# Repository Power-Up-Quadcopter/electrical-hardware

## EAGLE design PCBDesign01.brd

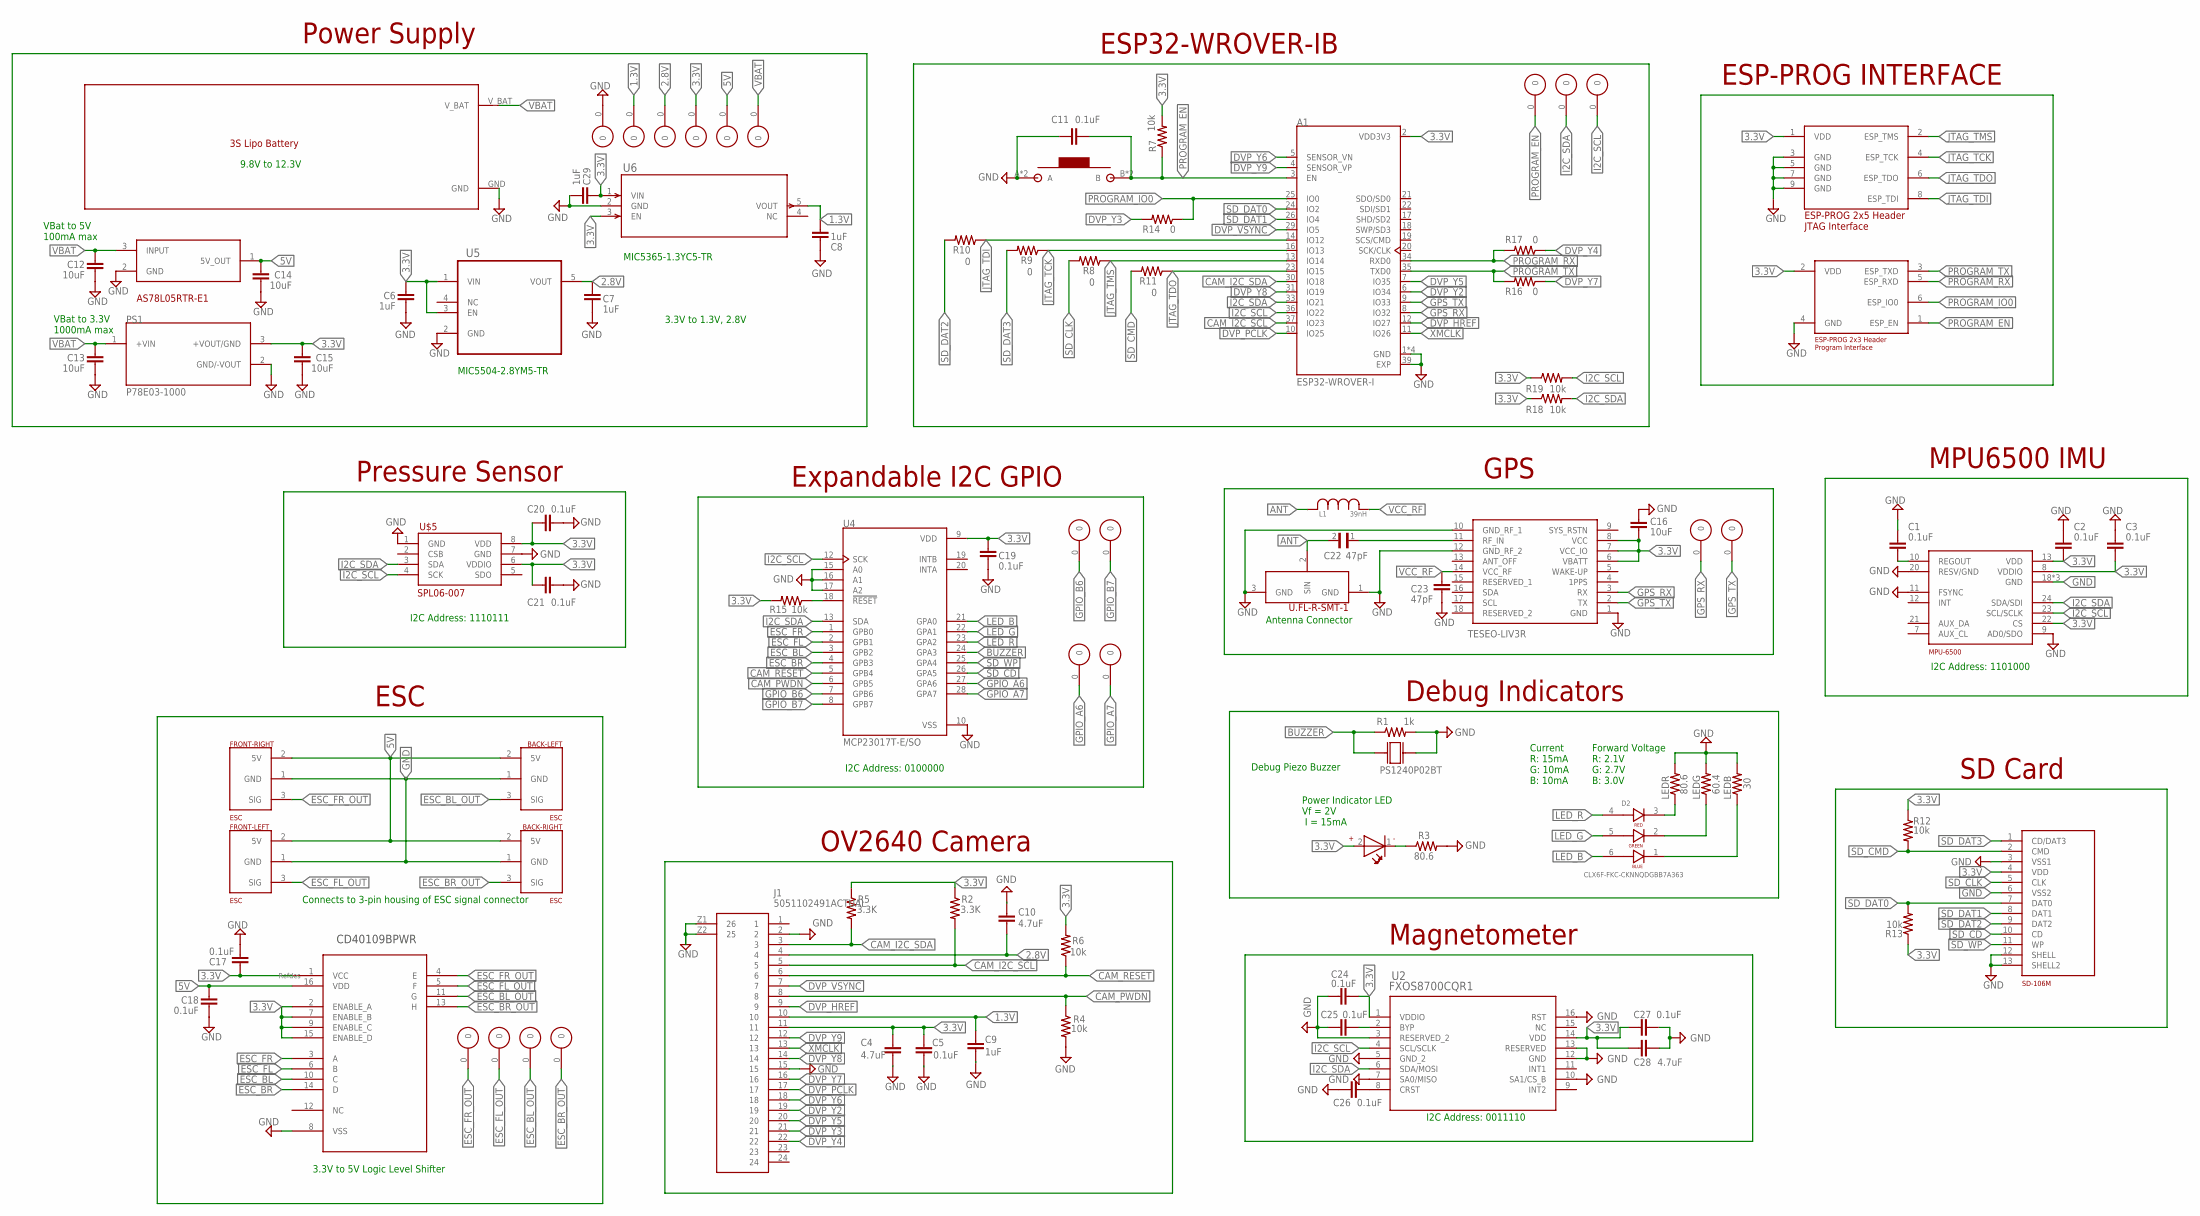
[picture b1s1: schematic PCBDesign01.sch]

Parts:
A1: ESP32-WROVER-I; XCVR_ESP32-WROVER-I
BACK-LEFT: ESC; MA03-1
BACK-RIGHT: ESC; MA03-1
BUZZER: PS1240P02BT; XDCR_PS1240P02BT
C1, C2, C3, C5, C11, C17, C18, C19, C20, C21, C24, C25, C26, C27: 0.1uF; CAPC2012X110
C4, C10, C28: 4.7uF; CAPC2012X110
C6, C7, C8, C9, C29: 1uF; CAPC2012X110
C12, C13, C14, C15, C16: 10uF; CAPC2012X110
C22: 47pF; CAPC1005X55N
C23: 47pF; CAPC2012X110
D2: CLX6F-FKC-CKNNQDGBB7A363; SOJ100P350X290-6N
FRONT-LEFT: ESC; MA03-1
FRONT-RIGHT: ESC; MA03-1
IC1: TESEO-LIV3R; TESEOLIV3R
J1: 5051102491ACTUAL; 687124149022
L1: 39nH; IND0402_22N_TAI_TAY-M
LEDB: 30; RESC2012X65
LEDG: 60.4; RESC2012X65
LEDR: 80.6; RESC2012X65
PS1: P78E03-1000; CONV_P78E03-1000
PWR-INDICATOR: WL-SMCW-150060GS75000-G; WL-SMCW_0603
R1: 1k; RESC2012X65
R2, R5: 3.3K; RESC2012X65
R3: 80.6; RESC2012X65
R4, R6, R7, R12, R13, R15, R18, R19: 10k; RESC2012X65
R8, R9, R10, R11, R14, R16, R17: 0; RESC2012X65
U2: FXOS8700CQR1; QFN16_3X3_NXP
U3: CD40109BPWR; SOP65P640X120-16N
U4: MCP23017T-E/SO; SOIC127P1030X265-28N
U5: MIC5504-2.8YM5-TR; SOT95P280X145-5N
U6: MIC5365-1.3YC5-TRSC-70_C5_MCH-M; SC-70_C5_MCH-M
U$1: MPU6500; QFN40P300X300X105-24N
U$2, U$9, U$10, U$11, U$12, U$13, U$14, U$15, U$16, U$17, U$18, U$19, U$20, U$21, U$23, U$24, U$25, U$26, U$27: TESTPOINT
U$3: SD-106M; SDCARD
U$4: U.FL-R-SMT-1; U.FL
U$5: SPL06-007
U$6: ESP-PROG_JTAG_HEADER; SAMTEC-FTS-105-01-X-D
U$7: ESP-PROG_PROGRAM_HEADER; SAMTEC-FTS-103-01-X-D
U$8: RESET; BUTTON
U$28: AS78L05RTR-E1; VREG_AP2204RA-3.3TRG1
U$29: LARGE_BATTERY

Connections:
1.3V: C8.1, C9.2, J1.10, U6.5 (VOUT), U$17.0
2.8V: C7.1, C10.1, J1.4, U5.5 (VOUT), U$18.0
3.3V: A1.2 (VDD3V3), C2.2, C3.2, C4.1, C5.1, C6.1, C15.2, C16.2, C17.2, C19.2, C20.2, C21.2, C24.2, C27.1, C28.1, C29.1, IC1.6 (VBATT), IC1.7 (VCC_IO), IC1.8 (VCC), J1.11, PS1.3 (+VOUT/GND), PWR-INDICATOR.2 (+), R2.1, R5.1, R6.2, R7.2, R12.1, R13.1, R15.2, R18.1, R19.1, U2.1 (VDDIO), U2.14 (VDD), U3.1 (VCC), U3.2 (ENABLE_A), U3.7 (ENABLE_B), U3.9 (ENABLE_C), U3.15 (ENABLE_D), U4.9 (VDD), U5.1 (VIN), U5.3 (EN), U6.1 (VIN), U6.3 (EN), U$1.8 (VDDIO), U$1.13 (VDD), U$1.22 (CS), U$3.4 (VDD), U$5.6 (VDDIO), U$5.8 (VDD), U$6.1 (VDD), U$7.2 (VDD), U$15.0
5V: BACK-LEFT.2 (5V), BACK-RIGHT.2 (5V), C14.2, C18.2, FRONT-LEFT.2 (5V), FRONT-RIGHT.2 (5V), U3.16 (VDD), U$16.0, U$28.1 (5V_OUT)
ANT: C22.2, L1.2, U$4.2 (SIN)
BUZZER: BUZZER.1, R1.1, U4.24 (GPA3)
CAM_I2C_SCL: A1.37 (IO23), J1.5, R2.2
CAM_I2C_SDA: A1.30 (IO18), J1.3, R5.2
CAM_PWDN: J1.8, R4.1, U4.6 (GPB5)
CAM_RESET: J1.6, R6.1, U4.5 (GPB4)
DVP_HREF: A1.12 (IO27), J1.9
DVP_PCLK: A1.10 (IO25), J1.17
DVP_VSYNC: A1.29 (IO5), J1.7
DVP_Y2: A1.6 (IO34), J1.19
DVP_Y3: J1.21, R14.2
DVP_Y4: J1.22, R17.1
DVP_Y5: A1.7 (IO35), J1.20
DVP_Y6: A1.5 (SENSOR_VN), J1.18
DVP_Y7: J1.16, R16.1
DVP_Y8: A1.31 (IO19), J1.14
DVP_Y9: A1.4 (SENSOR_VP), J1.12
ESC_BL: U3.10 (C), U4.3 (GPB2)
ESC_BL_OUT: BACK-LEFT.3 (SIG), U3.11 (G), U$25.0
ESC_BR: U3.14 (D), U4.4 (GPB3)
ESC_BR_OUT: BACK-RIGHT.3 (SIG), U3.13 (H), U$27.0
ESC_FL: U3.6 (B), U4.2 (GPB1)
ESC_FL_OUT: FRONT-LEFT.3 (SIG), U3.5 (F), U$26.0
ESC_FR: U3.3 (A), U4.1 (GPB0)
ESC_FR_OUT: FRONT-RIGHT.3 (SIG), U3.4 (E), U$24.0
GND: A1.1 (GND), A1.15 (GND), A1.38 (GND), A1.39 (EXP), A1.P$1 (GND), BACK-LEFT.1 (GND), BACK-RIGHT.1 (GND), BUZZER.2, C1.1, C2.1, C3.1, C4.2, C5.2, C6.2, C7.2, C8.2, C9.1, C10.2, C11.1, C12.1, C13.1, C14.1, C15.1, C16.1, C17.1, C18.1, C19.1, C20.1, C21.1, C23.1, C24.1, C25.2, C26.2, C27.2, C28.2, C29.2, FRONT-LEFT.1 (GND), FRONT-RIGHT.1 (GND), IC1.1 (GND), IC1.10 (GND_RF_1), IC1.12 (GND_RF_2), J1.2, J1.15, J1.Z1 (26), J1.Z2 (25), LEDB.2, LEDG.2, LEDR.2, PS1.2 (GND/-VOUT), R1.2, R3.2, R4.2, U2.3 (RESERVED_2), U2.5 (GND_2), U2.7 (SA0/MISO), U2.10 (SA1/CS_B), U2.12 (GND), U2.13 (RESERVED), U2.16 (RST), U3.8 (VSS), U4.10 (VSS), U4.15 (A0), U4.16 (A1), U4.17 (A2), U5.2 (GND), U6.2 (GND), U$1.9 (AD0/SDO), U$1.11 (FSYNC), U$1.18 (GND), U$1.20 (RESV/GND), U$1.25 (GND), U$1.P$1 (GND), U$3.3 (VSS1), U$3.6 (VSS2), U$3.12 (SHELL), U$3.13 (SHELL2), U$4.1 (GND), U$4.3 (GND), U$5.1 (GND), U$5.7 (GND), U$6.3 (GND), U$6.5 (GND), U$6.7 (GND), U$6.9 (GND), U$7.4 (GND), U$8.A, U$8.A@1 (A), U$21.0, U$28.2 (GND), U$29.GND
GPIO_A6: U4.27 (GPA6), U$2.0
GPIO_A7: U4.28 (GPA7), U$19.0
GPIO_B6: U4.7 (GPB6), U$14.0
GPIO_B7: U4.8 (GPB7), U$20.0
GPS_RX: A1.8 (IO32), IC1.3 (RX), U$11.0
GPS_TX: A1.9 (IO33), IC1.2 (TX), U$12.0
I2C_SCL: A1.36 (IO22), R19.2, U2.4 (SCL/SCLK), U4.12 (SCK), U$1.23 (SCL/SCLK), U$5.4 (SCK), U$10.0
I2C_SDA: A1.33 (IO21), R18.2, U2.6 (SDA/MOSI), U4.13 (SDA), U$1.24 (SDA/SDI), U$5.3 (SDA), U$9.0
JTAG_TCK: A1.16 (IO13), R9.1, U$6.4 (ESP_TCK)
JTAG_TDI: A1.14 (IO12), R10.1, U$6.8 (ESP_TDI)
JTAG_TDO: A1.23 (IO15), R11.1, U$6.6 (ESP_TDO)
JTAG_TMS: A1.13 (IO14), R8.1, U$6.2 (ESP_TMS)
LED_B: D2.6, U4.21 (GPA0)
LED_G: D2.5, U4.22 (GPA1)
LED_R: D2.4, U4.23 (GPA2)
unnamed: D2.3, LEDR.1
unnamed: D2.2, LEDG.1
unnamed: C1.2, U$1.10 (REGOUT)
unnamed: D2.1, LEDB.1
unnamed: C26.1, U2.8 (CRST)
unnamed: PWR-INDICATOR.1 (-), R3.1
unnamed: C25.1, U2.2 (BYP)
unnamed: C22.1, IC1.11 (RF_IN)
unnamed: R15.1, U4.18 (!RESET)
PROGRAM_EN: A1.3 (EN), C11.2, R7.1, U$7.1 (ESP_EN), U$8.B, U$8.B@1 (B), U$23.0
PROGRAM_IO0: A1.25 (IO0), R14.1, U$7.6 (ESP_IO0)
PROGRAM_RX: A1.34 (RXD0), R17.2, U$7.5 (ESP_RXD)
PROGRAM_TX: A1.35 (TXD0), R16.2, U$7.3 (ESP_TXD)
SD_CD: U4.26 (GPA5), U$3.10 (CD)
SD_CLK: R8.2, U$3.5 (CLK)
SD_CMD: R11.2, R12.2, U$3.2 (CMD)
SD_DAT0: A1.24 (IO2), R13.2, U$3.7 (DAT0)
SD_DAT1: A1.26 (IO4), U$3.8 (DAT1)
SD_DAT2: R10.2, U$3.9 (DAT2)
SD_DAT3: R9.2, U$3.1 (CD/DAT3)
SD_WP: U4.25 (GPA4), U$3.11 (WP)
VBAT: C12.2, C13.2, PS1.1 (+VIN), U$13.0, U$28.3 (INPUT), U$29.V_BAT
VCC_RF: C23.2, IC1.14 (VCC_RF), L1.1
XMCLK: A1.11 (IO26), J1.13

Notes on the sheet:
I2C Address: 1101000
Current R: 15mA G: 10mA B: 10mA
Forward Voltage R: 2.1V G: 2.7V B: 3.0V
Power Indicator LED Vf = 2V I = 15mA
3.3V to 1.3V, 2.8V
9.8V to 12.3V
VBat to 3.3V 1000mA max
Power Supply
Debug Piezo Buzzer
OV2640 Camera
SD Card
Debug Indicators
MPU6500 IMU
GPS
Antenna Connector
ESP32-WROVER-IB
ESP-PROG INTERFACE
3.3V to 5V Logic Level Shifter
Connects to 3-pin housing of ESC signal connector
ESC
Expandable I2C GPIO
I2C Address: 1110111
Pressure Sensor
I2C Address: 0100000
VBat to 5V 100mA max
I2C Address: 0011110
Magnetometer
MIC5365-1.3YC5-TR
MIC5504-2.8YM5-TR

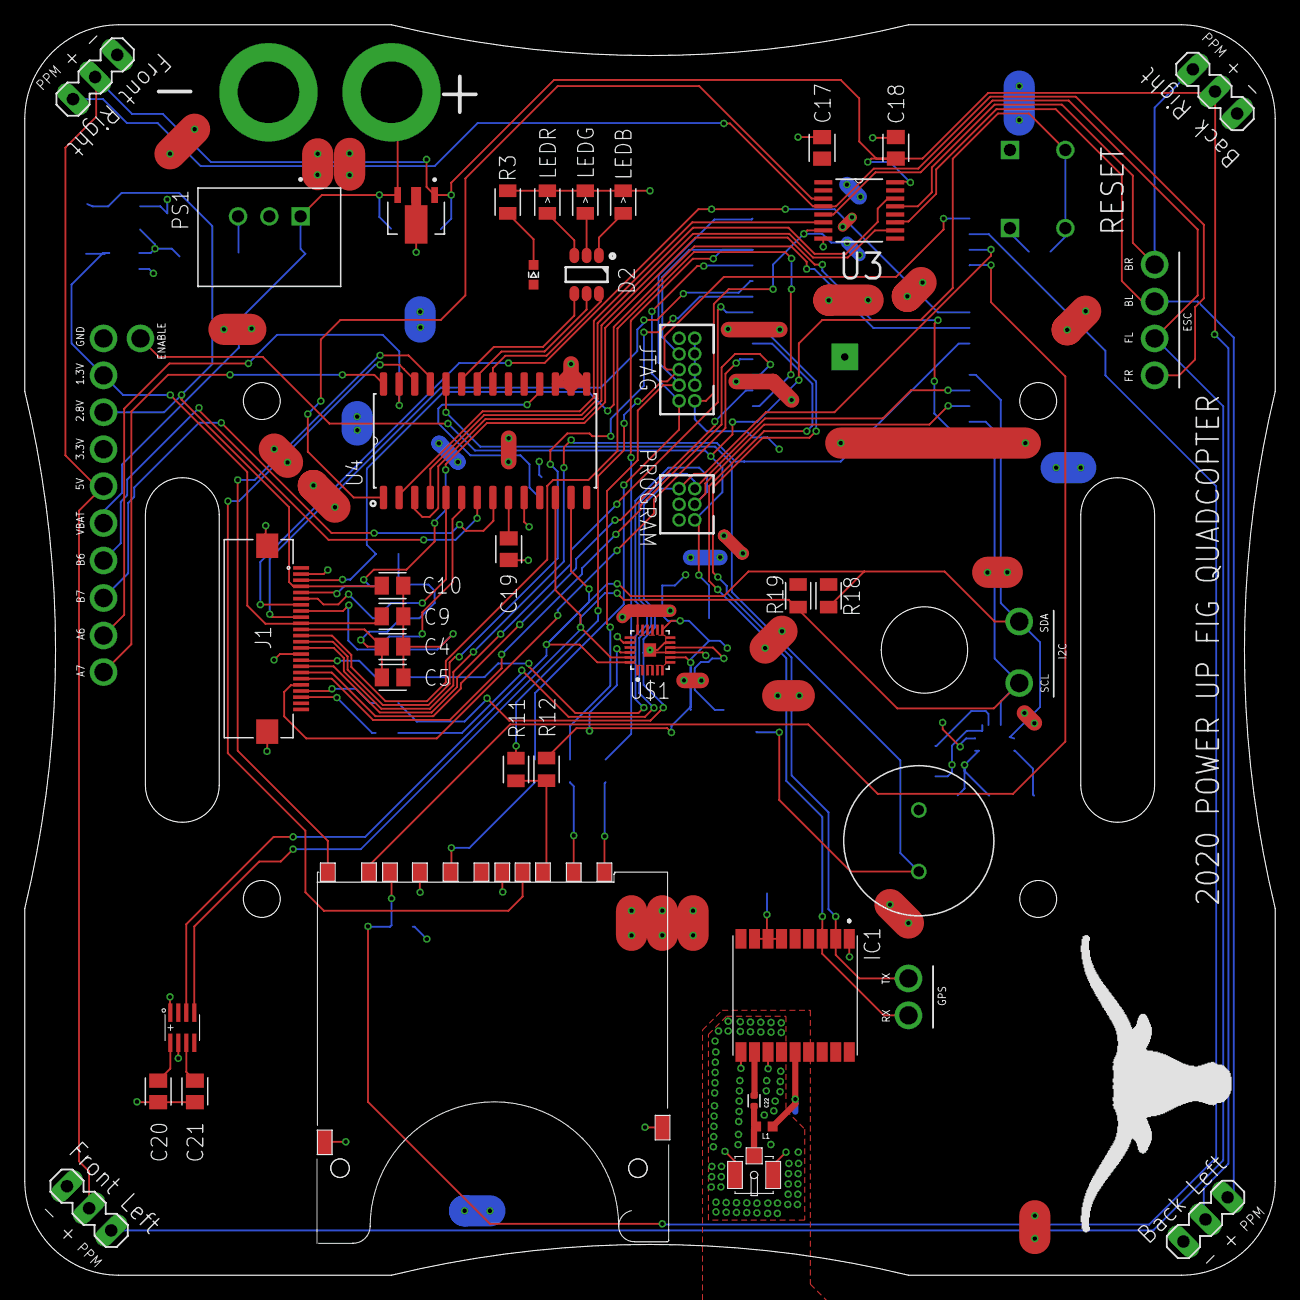
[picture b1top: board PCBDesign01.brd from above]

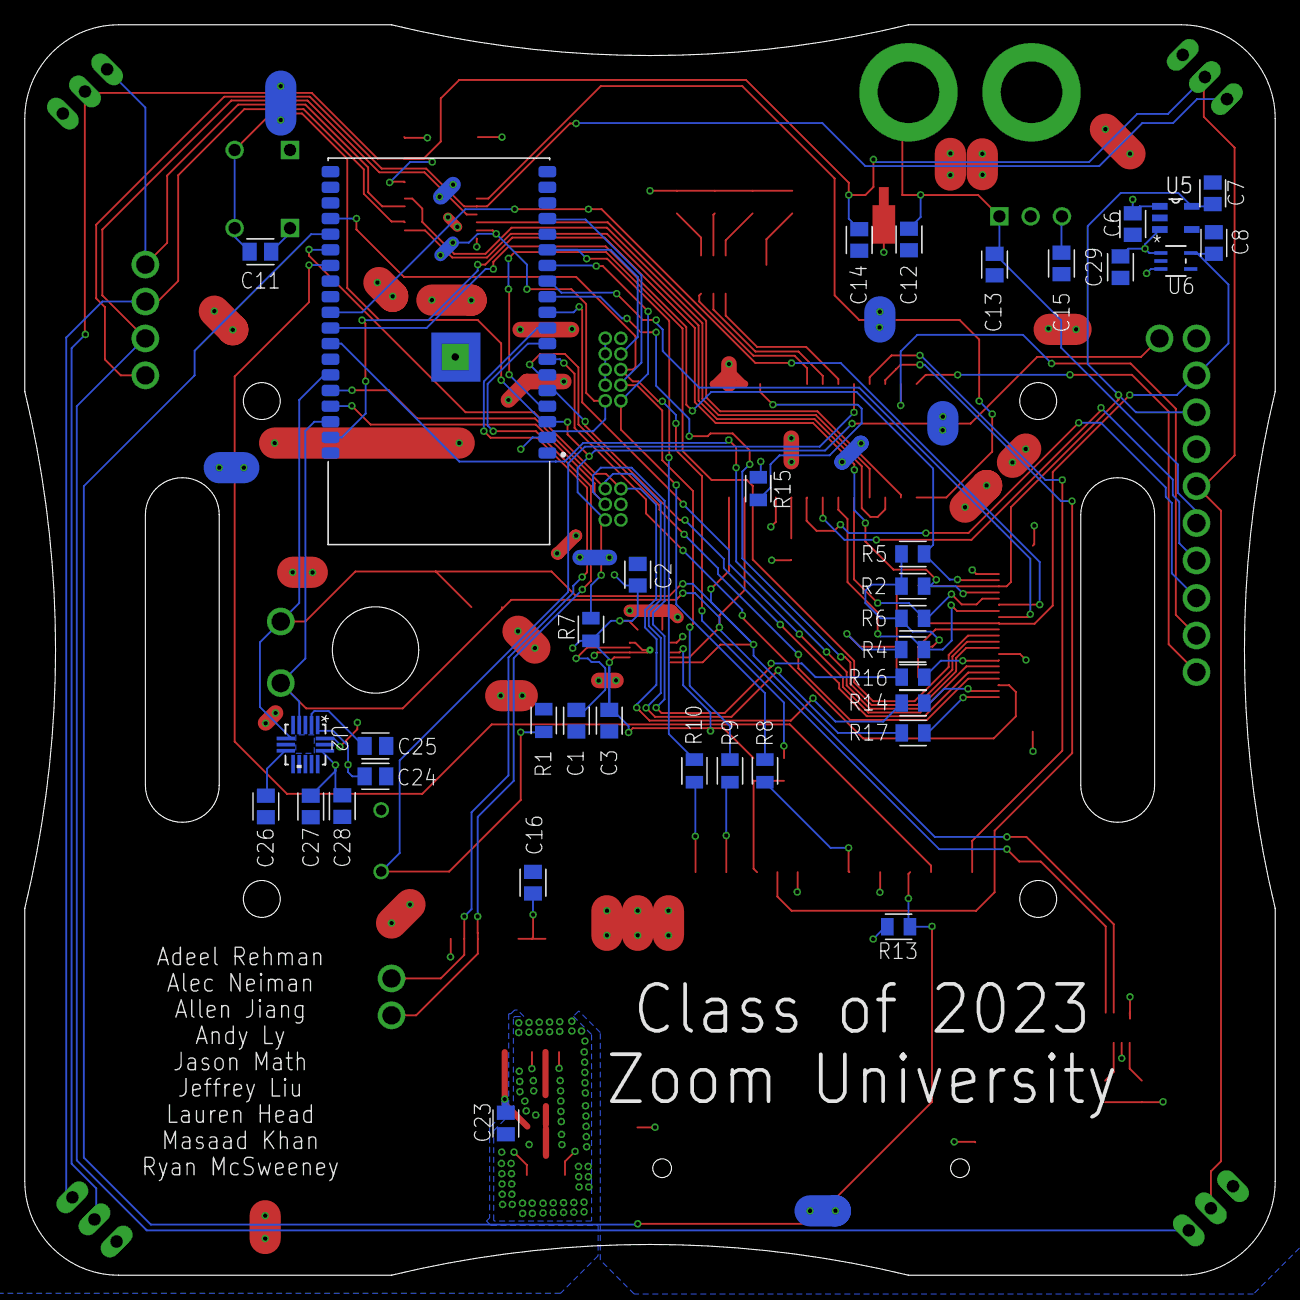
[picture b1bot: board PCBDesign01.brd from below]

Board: 2 copper layers, 101.6 x 101.6 mm, 96 parts (37 on the bottom side), 69 nets.

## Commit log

2020-05-17 Base files
2020-05-19 Added Required Libraries
2020-05-20 Added data sheets and connected some pins
2020-05-21 more stuff
2020-05-24 moar
2020-05-24 Update datsheets
2020-05-24 minor resistor changes
2020-05-25 pressure sensor
2020-05-26 doing pcb layout
2020-05-27 ready for pcb review
2020-05-28 add magnetometer
2020-05-29 verification
2020-06-02 names
2020-06-02 smol edits
2020-06-02 minor adjustments
2020-06-03 final?
2020-06-03 final.
2020-06-03 final final
2020-06-03 color
2021-02-19 i think i changed a cap

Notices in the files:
parts and their libraries:
COPYRIGHT: Copyright (C) 2018 Accelerated Designs. All rights reserved
